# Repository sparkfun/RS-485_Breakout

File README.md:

SparkFun Transceiver RS-485 Breakout
====================================

[
*RS-485 Breakout (BOB-10124)*](https://www.sparkfun.com/products/10124)

This is a breakout for the SP3485 RS-485 transceiver IC. This will convert a UART serial stream to RS-485. 

Repository Contents
-------------------

* **/Hardware** - All Eagle design files (.brd, .sch, .STL)
* **/Production** - Test bed files and production panel files 

Documentation
--------------
* **[SparkFun 3D Model repo](https://github.com/sparkfun/3D_Models)** - 3D models of SparkFun products. 

License Information
-------------------
The hardware is released under [Creative Commons ShareAlike 4.0 International](https://creativecommons.org/licenses/by-sa/4.0/).
The code is beerware; if you see me (or any other SparkFun employee) at the local, and you've found our code helpful, please buy us a round!

Distributed as-is; no warranty is given.

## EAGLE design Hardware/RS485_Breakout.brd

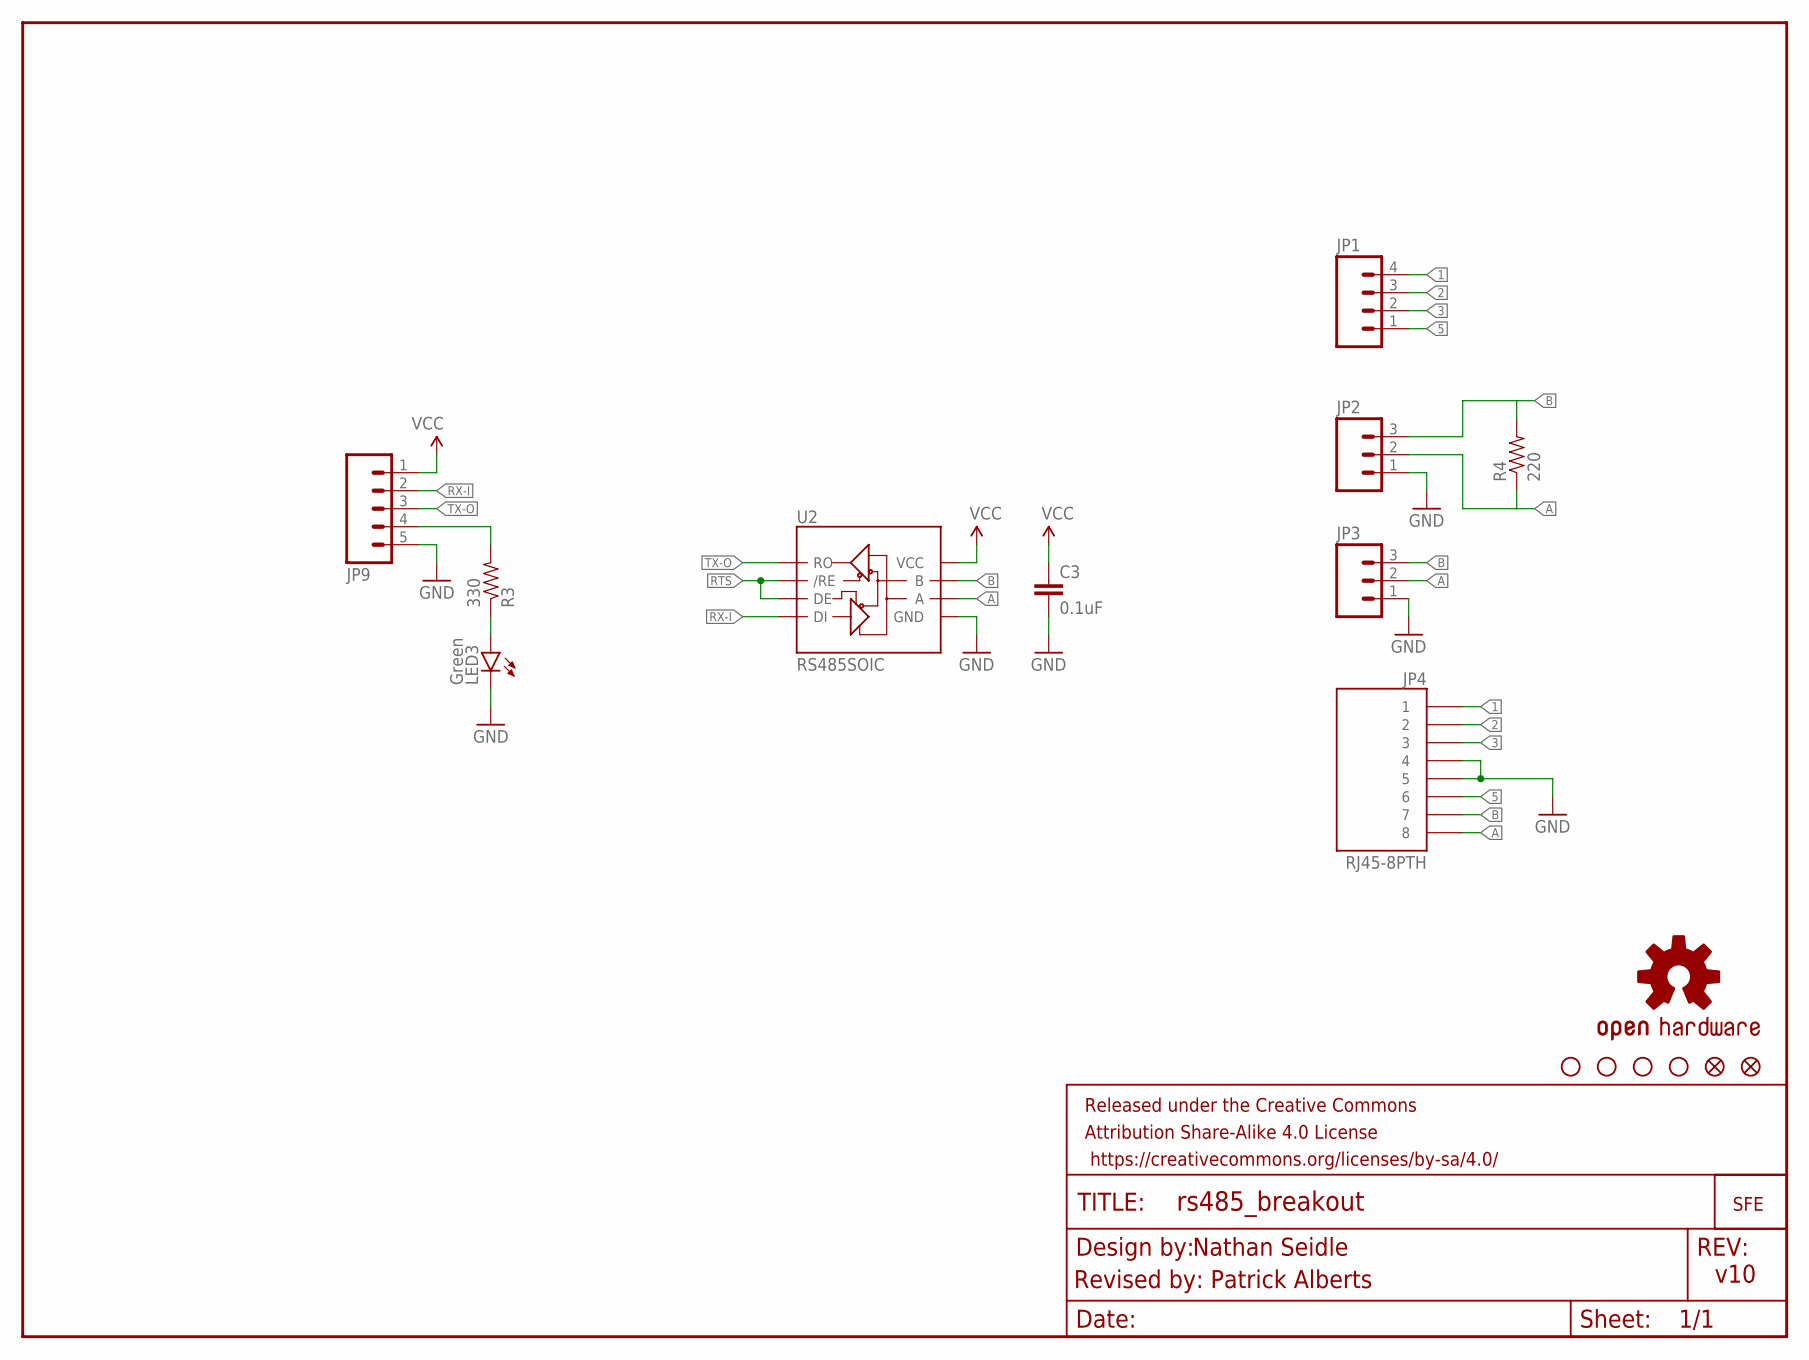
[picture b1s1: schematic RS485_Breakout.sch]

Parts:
C3: 0.1uF; 0603-CAP
FRAME1: FRAME-LETTER; CREATIVE_COMMONS
JP1: M04PTH; 1X04
JP2: M03SCREW; SCREWTERMINAL-3.5MM-3
JP3: M03PTH; 1X03
JP4: RJ45-8PTH; RJ45-8
JP5, JP10: FIDUCIAL1X2; FIDUCIAL-1X2
JP6, JP7, JP8, JP15: STAND-OFF
JP9: M05PTH; 1X05
LED3: Green; LED-0603
LOGO1: OSHW-LOGOS; OSHW-LOGO-S
R3: 330; 0603-RES
R4: 220; 0603-RES
U2: RS485SOIC; SO08
U$2: LOGO-SFESK; SFE-LOGO-FLAME

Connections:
1: JP1.4, JP4.1
2: JP1.3, JP4.2
3: JP1.2, JP4.3
5: JP1.1, JP4.6
A: JP2.2, JP3.2, JP4.8, R4.1, U2.6 (A)
B: JP2.3, JP3.3, JP4.7, R4.2, U2.7 (B)
GND: C3.2, JP2.1, JP3.1, JP4.4, JP4.5, JP9.5, LED3.C, U2.5 (GND)
unnamed: LED3.A, R3.1
RTS: JP9.4, R3.2, U2.2 (/RE), U2.3 (DE)
RX-I: JP9.2, U2.4 (DI)
TX-O: JP9.3, U2.1 (RO)
VCC: C3.1, JP9.1, U2.8 (VCC)

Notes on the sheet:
v10
Nathan Seidle
Revised by: Patrick Alberts

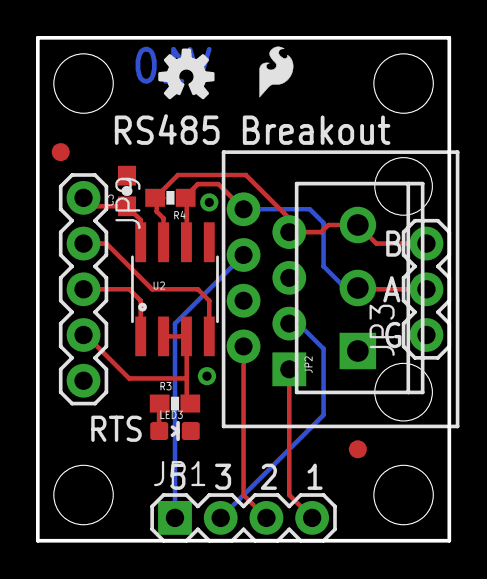
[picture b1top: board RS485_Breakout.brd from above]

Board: 2 copper layers, 22.9 x 27.9 mm, 19 parts (0 on the bottom side), 12 nets.

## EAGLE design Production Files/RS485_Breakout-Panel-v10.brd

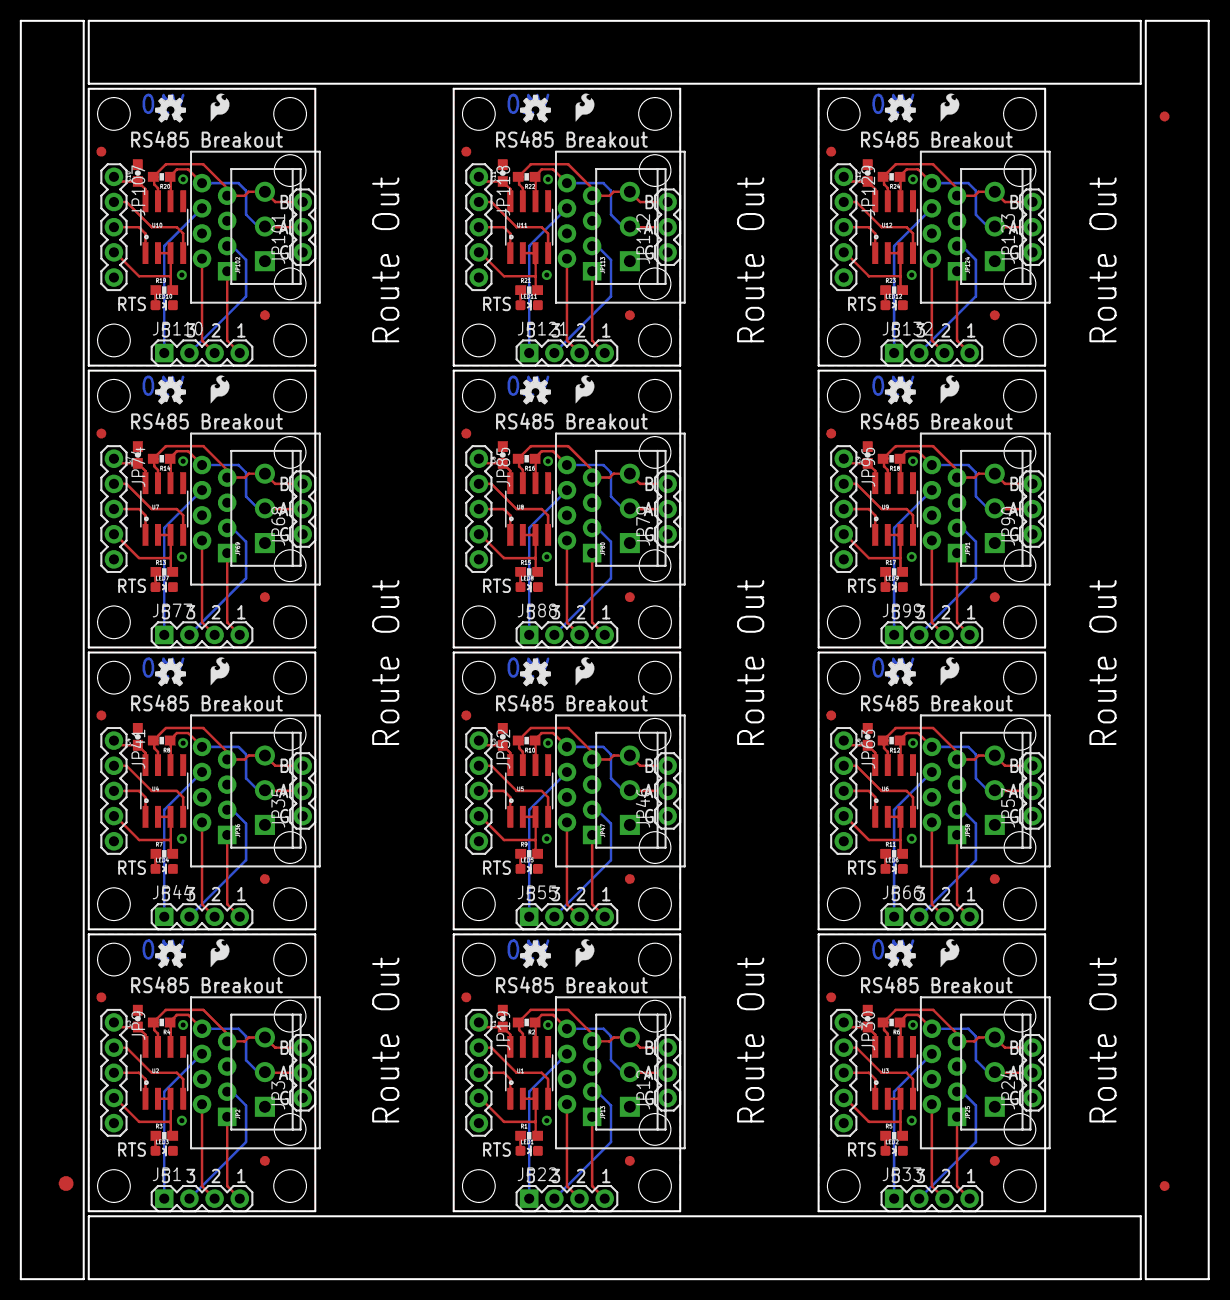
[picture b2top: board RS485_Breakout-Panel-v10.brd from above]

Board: 2 copper layers, 119.9 x 127.0 mm, 219 parts (0 on the bottom side), 144 nets.

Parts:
C1, C2, C3, C4, C5, C6, C7, C8, C9, C10, C11, C12: 0.1uF; 0603-CAP
E$1: FIDUCIAL-1.5X3
E$7, E$8: FIDUCIAL-1X2
JP1, JP22, JP33, JP44, JP55, JP66, JP77, JP88, JP99, JP110, JP121, JP132: 1X04
JP2, JP13, JP25, JP36, JP47, JP58, JP69, JP80, JP91, JP102, JP113, JP124: SCREWTERMINAL-3.5MM-3
JP3, JP12, JP24, JP35, JP46, JP57, JP68, JP79, JP90, JP101, JP112, JP123: 1X03
JP4, JP11, JP23, JP34, JP45, JP56, JP67, JP78, JP89, JP100, JP111, JP122: RJ45-8PTH; RJ45-8
JP5, JP10, JP20, JP21, JP31, JP32, JP42, JP43, JP53, JP54, JP64, JP65, JP75, JP76, JP86, JP87, JP97, JP98, JP108, JP109, JP119, JP120, JP130, JP131: FIDUCIAL1X2; FIDUCIAL-1X2
JP6, JP7, JP8, JP14, JP15, JP16, JP17, JP18, JP26, JP27, JP28, JP29, JP37, JP38, JP39, JP40, JP48, JP49, JP50, JP51, JP59, JP60, JP61, JP62, JP70, JP71, JP72, JP73, JP81, JP82, JP83, JP84, JP92, JP93, JP94, JP95, JP103, JP104, JP105, JP106, JP114, JP115, JP116, JP117, JP125, JP126, JP127, JP128: STAND-OFF
JP9, JP19, JP30, JP41, JP52, JP63, JP74, JP85, JP96, JP107, JP118, JP129: 1X05
LED1, LED2, LED3, LED4, LED5, LED6, LED7, LED8, LED9, LED10, LED11, LED12: Green; LED-0603
LOGO1, LOGO2, LOGO3, LOGO4, LOGO5, LOGO6, LOGO7, LOGO8, LOGO9, LOGO10, LOGO11, LOGO12: OSHW-LOGOS; OSHW-LOGO-S
R1, R3, R5, R7, R9, R11, R13, R15, R17, R19, R21, R23: 330; 0603-RES
R2, R4, R6, R8, R10, R12, R14, R16, R18, R20, R22, R24: 220; 0603-RES
U1, U2, U3, U4, U5, U6, U7, U8, U9, U10, U11, U12: RS485SOIC; SO08
U$1, U$2, U$3, U$4, U$5, U$6, U$7, U$8, U$9, U$10, U$11, U$12: LOGO-SFESK; SFE-LOGO-FLAME

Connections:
1: JP1.4, JP4.1
2: JP1.3, JP4.2
3: JP1.2, JP4.3
4: JP11.1, JP22.4
5: JP1.1, JP4.6
6: JP11.2, JP22.3
7: JP11.3, JP22.2
8: JP11.6, JP22.1
9: JP23.1, JP33.4
10: JP23.2, JP33.3
11: JP23.3, JP33.2
12: JP23.6, JP33.1
13: JP34.1, JP44.4
14: JP34.2, JP44.3
15: JP34.3, JP44.2
16: JP34.6, JP44.1
17: JP45.1, JP55.4
18: JP45.2, JP55.3
19: JP45.3, JP55.2
20: JP45.6, JP55.1
21: JP56.1, JP66.4
22: JP56.2, JP66.3
23: JP56.3, JP66.2
24: JP56.6, JP66.1
25: JP67.1, JP77.4
26: JP67.2, JP77.3
27: JP67.3, JP77.2
28: JP67.6, JP77.1
29: JP78.1, JP88.4
30: JP78.2, JP88.3
31: JP78.3, JP88.2
32: JP78.6, JP88.1
33: JP89.1, JP99.4
34: JP89.2, JP99.3
35: JP89.3, JP99.2
36: JP89.6, JP99.1
37: JP100.1, JP110.4
38: JP100.2, JP110.3
39: JP100.3, JP110.2
40: JP100.6, JP110.1
41: JP111.1, JP121.4
42: JP111.2, JP121.3
43: JP111.3, JP121.2
44: JP111.6, JP121.1
45: JP122.1, JP132.4
46: JP122.2, JP132.3
47: JP122.3, JP132.2
48: JP122.6, JP132.1
A: JP2.2, JP3.2, JP4.8, R4.1, U2.6
A1: JP11.8, JP12.2, JP13.2, R2.1, U1.6
A2: JP23.8, JP24.2, JP25.2, R6.1, U3.6
A3: JP34.8, JP35.2, JP36.2, R8.1, U4.6
A4: JP45.8, JP46.2, JP47.2, R10.1, U5.6
A5: JP56.8, JP57.2, JP58.2, R12.1, U6.6
A6: JP67.8, JP68.2, JP69.2, R14.1, U7.6
A7: JP78.8, JP79.2, JP80.2, R16.1, U8.6
A8: JP89.8, JP90.2, JP91.2, R18.1, U9.6
A9: JP100.8, JP101.2, JP102.2, R20.1, U10.6
A10: JP111.8, JP112.2, JP113.2, R22.1, U11.6
A11: JP122.8, JP123.2, JP124.2, R24.1, U12.6
B: JP2.3, JP3.3, JP4.7, R4.2, U2.7
B1: JP11.7, JP12.3, JP13.3, R2.2, U1.7
B2: JP23.7, JP24.3, JP25.3, R6.2, U3.7
B3: JP34.7, JP35.3, JP36.3, R8.2, U4.7
B4: JP45.7, JP46.3, JP47.3, R10.2, U5.7
B5: JP56.7, JP57.3, JP58.3, R12.2, U6.7
B6: JP67.7, JP68.3, JP69.3, R14.2, U7.7
B7: JP78.7, JP79.3, JP80.3, R16.2, U8.7
B8: JP89.7, JP90.3, JP91.3, R18.2, U9.7
B9: JP100.7, JP101.3, JP102.3, R20.2, U10.7
B10: JP111.7, JP112.3, JP113.3, R22.2, U11.7
B11: JP122.7, JP123.3, JP124.3, R24.2, U12.7
GND: C3.2, JP2.1, JP3.1, JP4.4, JP4.5, JP9.5, LED3.C, U2.5
GND1: C1.2, JP11.4, JP11.5, JP12.1, JP13.1, JP19.5, LED1.C, U1.5
GND2: C2.2, JP23.4, JP23.5, JP24.1, JP25.1, JP30.5, LED2.C, U3.5
GND3: C4.2, JP34.4, JP34.5, JP35.1, JP36.1, JP41.5, LED4.C, U4.5
GND4: C5.2, JP45.4, JP45.5, JP46.1, JP47.1, JP52.5, LED5.C, U5.5
GND5: C6.2, JP56.4, JP56.5, JP57.1, JP58.1, JP63.5, LED6.C, U6.5
GND6: C7.2, JP67.4, JP67.5, JP68.1, JP69.1, JP74.5, LED7.C, U7.5
GND7: C8.2, JP78.4, JP78.5, JP79.1, JP80.1, JP85.5, LED8.C, U8.5
GND8: C9.2, JP89.4, JP89.5, JP90.1, JP91.1, JP96.5, LED9.C, U9.5
GND9: C10.2, JP100.4, JP100.5, JP101.1, JP102.1, JP107.5, LED10.C, U10.5
GND10: C11.2, JP111.4, JP111.5, JP112.1, JP113.1, JP118.5, LED11.C, U11.5
GND11: C12.2, JP122.4, JP122.5, JP123.1, JP124.1, JP129.5, LED12.C, U12.5
unnamed: LED1.A, R1.1
unnamed: LED2.A, R5.1
unnamed: LED4.A, R7.1
unnamed: LED3.A, R3.1
unnamed: LED5.A, R9.1
unnamed: LED6.A, R11.1
unnamed: LED7.A, R13.1
unnamed: LED8.A, R15.1
unnamed: LED9.A, R17.1
unnamed: LED10.A, R19.1
unnamed: LED11.A, R21.1
unnamed: LED12.A, R23.1
RTS: JP9.4, R3.2, U2.2, U2.3
RTS1: JP19.4, R1.2, U1.2, U1.3
RTS2: JP30.4, R5.2, U3.2, U3.3
RTS3: JP41.4, R7.2, U4.2, U4.3
RTS4: JP52.4, R9.2, U5.2, U5.3
RTS5: JP63.4, R11.2, U6.2, U6.3
RTS6: JP74.4, R13.2, U7.2, U7.3
RTS7: JP85.4, R15.2, U8.2, U8.3
RTS8: JP96.4, R17.2, U9.2, U9.3
RTS9: JP107.4, R19.2, U10.2, U10.3
RTS10: JP118.4, R21.2, U11.2, U11.3
RTS11: JP129.4, R23.2, U12.2, U12.3
RX-I: JP9.2, U2.4
RX-I1: JP19.2, U1.4
RX-I2: JP30.2, U3.4
RX-I3: JP41.2, U4.4
RX-I4: JP52.2, U5.4
RX-I5: JP63.2, U6.4
RX-I6: JP74.2, U7.4
RX-I7: JP85.2, U8.4
RX-I8: JP96.2, U9.4
RX-I9: JP107.2, U10.4
RX-I10: JP118.2, U11.4
RX-I11: JP129.2, U12.4
TX-O: JP9.3, U2.1
TX-O1: JP19.3, U1.1
TX-O2: JP30.3, U3.1
TX-O3: JP41.3, U4.1
TX-O4: JP52.3, U5.1
TX-O5: JP63.3, U6.1
TX-O6: JP74.3, U7.1
TX-O7: JP85.3, U8.1
TX-O8: JP96.3, U9.1
TX-O9: JP107.3, U10.1
TX-O10: JP118.3, U11.1
TX-O11: JP129.3, U12.1
VCC: C3.1, JP9.1, U2.8
VCC1: C1.1, JP19.1, U1.8
VCC2: C2.1, JP30.1, U3.8
VCC3: C4.1, JP41.1, U4.8
VCC4: C5.1, JP52.1, U5.8
VCC5: C6.1, JP63.1, U6.8
VCC6: C7.1, JP74.1, U7.8
VCC7: C8.1, JP85.1, U8.8
VCC8: C9.1, JP96.1, U9.8
VCC9: C10.1, JP107.1, U10.8
VCC10: C11.1, JP118.1, U11.8
VCC11: C12.1, JP129.1, U12.8

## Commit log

2014-06-24 Initial commit with brd/sch
2014-06-24 Updated to entire board
    upgraded to 0603, frame letter sch, added oshw logo, cleaned up traces
    and added version #.
2014-06-25 Silk Change
2014-07-01 Sch Change
2014-09-18 created panel v10
    spaced accordingly for selective soldering
2014-12-15 Updating README, adding .gitignore
2016-02-29 Updated README
    This part has a 3D Model. 3D Model Repo link added.

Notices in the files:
parts and their libraries:
SparkFun-LED: Licensing: Creative Commons ShareAlike 4.0 International - https://creativecommons.org/licenses/by-sa/4.0
SparkFun-Aesthetics: Released under the Creative Commons Attribution Share-Alike 4.0 License
SparkFun-Aesthetics: Released under the Creative Commons
